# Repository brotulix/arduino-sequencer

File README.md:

# arduino-sequencer
A simple Arduino-based sequencer to turn masthead preamplifier and power amplifier on and off in sequence when beginning and ending transmission, as well as inhibiting transmit on a Yaesu radio (FT-991 or FT-817).

Additions will be switching coax relays to allow co-listening with an SDR during receive period.

## PTT

The same sequencer is intended for 144 and 432 MHz operation, for which I own power amplifiers with opposite PTT controls; one will activate when PTT is pulled high, one will activate when PTT is pulled low. To solve this with the least hassle, I'll control the PTT using a photo diode surrounded by four diodes, and select active high or active low using a toggle switch:

Here, J1 (an RCA socket) connects to the PTT input of either KLM electronics VHF PA or Microwave Modules MML 432/100 UHF PA. SW1 is DPDT and will flip voltages for both the opto-coupler and the pull up/down.

# State machine
So, a state machine may be a useful method to keep track of where one is in the sequence of events going from RX -> TX or TX -> RX.

Maybe some form of table-based state machine to easily add stages and transitioning to the right next state?

Whether I'll use an interrupt to trigger on flank or simply evaluate high/low state in a loop is TBD.

## Initialization / Power-up
The system starts up in an unknown state as of yet. I think it should sets some signals to a safe-ish state immediately, then progresses through some sequence of events to reach a true RX state.

Probably the most important detail is that the PA should be switched on after the sequencer.

> Should the radio be switched on after the sequencer, too, to make sure TX inhibit is on from the start?

## RX -> TX
The sequence when going from RX to TX is something like this:

### RX -> TX -> RX
The special case when TX goes low before during the transition from RX to TX should go something like this:

See *dwell time*.

## TX -> RX
Transitioning from TX back to RX:

### TX -> RX -> TX
The special case where one is transmitting, but then experience a glitch in TX from radio which begins a transition to RX, but then returns to TX during the transition phase.

See *dwell time*.

# Dwell time
> Add a potensiometer/encoder to set the delay for each stage? First design may use the same delay for both entering and leaving transmit state, but perhaps allow for faster delays going one direction or the other later?

Upon entering every state, set a minimum dwell time for that state to allow for energy to stabilize in the system (eg. DC bias for preamp; depending on coax length, you may want a certain minimum delay to allow the rising edge to reach full round-trip).

This may remove the need for a "inter-state" delay period, and depending on what the Radio TX signal is when entering (or exiting) the state determines which direction one goes. So, in principle, by toggling TX line fast enough, it may be possible to stay in the twilight zone between RX and TX indefinitely?

# Blinkenlights
I'm thinking a front panel that shows what state the in- and outputs are in. Should at least help during development when the timing probably is way longer than necessary.

The idea here is that when idle, only the green RX LED should light up. Then, when the radio activates the TX line, the red TX LED lights up, rendering the LED yellow-ish. While both of these LEDs are lit, the individual output LEDs on the side should light up from the bottom up, until all are lit, when the green RX LED goes out and only the red TX LED is lit.

> Perhaps also have the individual stages as red/green LEDs to more clearly illustrate the logic colour-code?

> Perhaps also have a fancy display that shows the current delay count-down for that extra *ooh* and *aah*, at least during development?

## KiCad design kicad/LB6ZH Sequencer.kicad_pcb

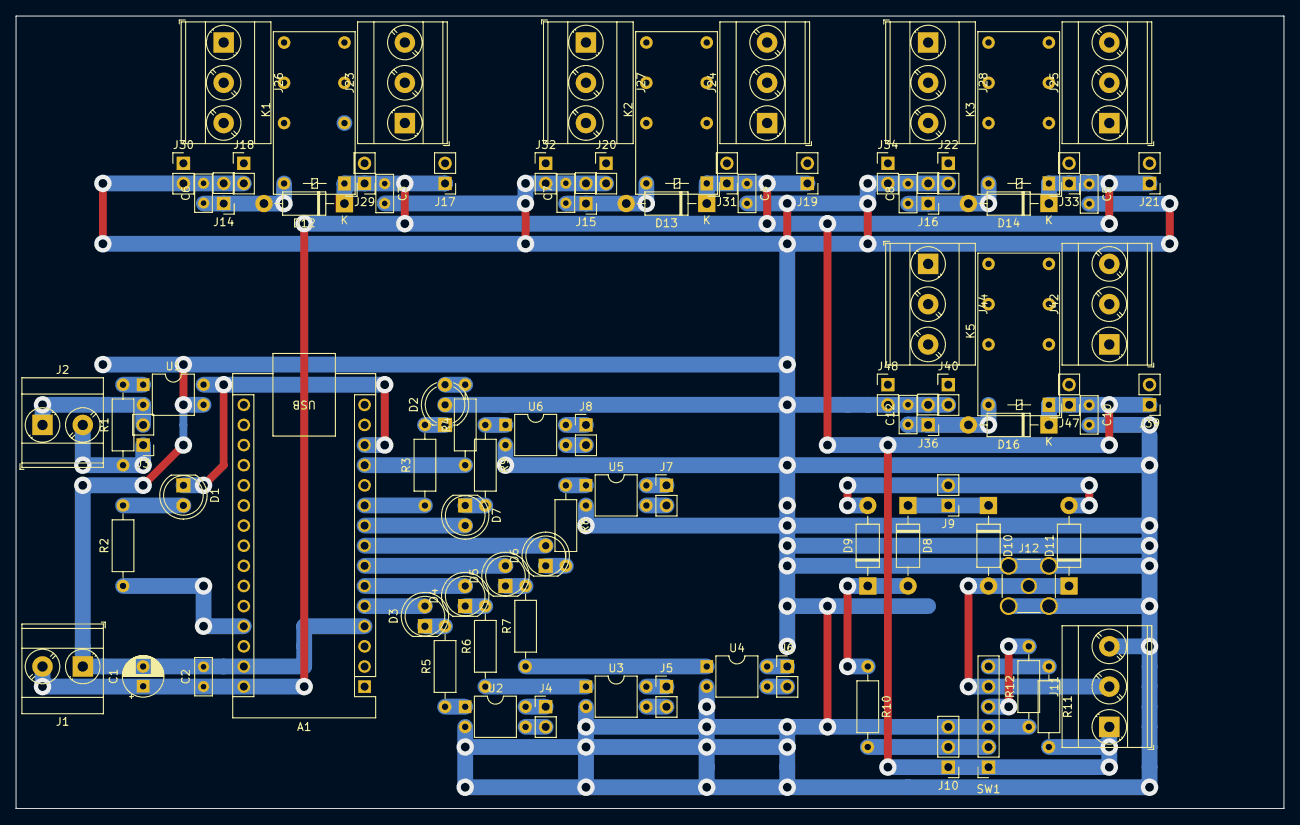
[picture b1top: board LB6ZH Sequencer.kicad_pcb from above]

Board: 2 copper layers, 160.0 x 100.0 mm, 89 parts (0 on the bottom side), 67 nets.

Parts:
A1: Arduino_Nano_Every; Arduino_Nano
C1: 100u; CP_Radial_D5.0mm_P2.50mm
C2, C3, C4, C5, C6, C7, C8, C10, C12: 10n; C_Rect_L4.6mm_W2.0mm_P2.50mm_MKS02_FKP02
D1: RD; LED_D5.0mm_Clear
D2: LED_Dual_AKA; LED_D5.0mm-3
D3, D4, D5, D6, D7: YE; LED_D5.0mm_Clear
D8, D9, D10, D11, D12, D13, D14, D16: 1N4001; D_DO-41_SOD81_P10.16mm_Horizontal
J1: 1x2; TerminalBlock_Phoenix_MKDS-3-2-5.08_1x02_P5.08mm_Horizontal
J2: Screw_Terminal_01x02; TerminalBlock_Phoenix_MKDS-3-2-5.08_1x02_P5.08mm_Horizontal
J3, J4, J5, J6, J7, J8, J9, J14, J15, J16, J17, J18, J19, J20, J21, J22, J29, J30, J31, J32, J33, J34, J36, J39, J40, J47, J48: Conn_01x02; PinHeader_1x02_P2.54mm_Vertical
J10: Conn_01x03; PinHeader_1x03_P2.54mm_Vertical
J11, J23, J24, J25, J26, J27, J28, J42, J44: 1x3; TerminalBlock_Phoenix_MKDS-3-3-5.08_1x03_P5.08mm_Horizontal
J12: RCA; SMA_Amphenol_901-144_Vertical
K1, K2, K3, K5: FINDER-30.22; Relay_DPDT_Finder_30.22
R1: 680R; R_Axial_DIN0207_L6.3mm_D2.5mm_P10.16mm_Horizontal
R2: 150R; R_Axial_DIN0207_L6.3mm_D2.5mm_P10.16mm_Horizontal
R3, R4, R5, R6, R7, R8, R9: 82R; R_Axial_DIN0207_L6.3mm_D2.5mm_P10.16mm_Horizontal
R10: 1k; R_Axial_DIN0207_L6.3mm_D2.5mm_P10.16mm_Horizontal
R11, R12: 10k; R_Axial_DIN0207_L6.3mm_D2.5mm_P10.16mm_Horizontal
SW1: SW_DPDT_x2; PinSocket_1x06_P2.54mm_Vertical
U1, U2, U3, U4, U5, U6: PC817; DIP-4_W7.62mm

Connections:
5V: A1.27 (+5V), R2.1
COAX_A: A1.6 (D3), D4.2 (A)
COAX_B: A1.7 (D4), D5.2 (A)
GND: A1.4 (GND), A1.29 (GND), C1.2, C2.2, C3.2, C4.2, C5.2, C6.2, C7.2, C8.2, C10.2, C12.2, D2.2 (K), J1.1, J10.3, J11.3, J12.2 (Ext), J14.2, J15.2, J16.2, J18.2, J20.2, J22.2, J30.2, J32.2, J34.2, J36.2, J40.2, J48.2, R12.1, SW1.3 (C), U1.3, U2.2, U3.2, U4.2, U5.2, U6.2
unnamed: A1.13 (D10), D1.1 (K), U1.4
unnamed: D1.2 (A), R2.2
unnamed: D2.1 (A1), R3.2
unnamed: D2.3 (A2), R4.2
unnamed: D3.1 (K), R5.2
unnamed: D4.1 (K), R6.2
unnamed: D5.1 (K), R7.2
unnamed: D6.1 (K), R8.2
unnamed: D7.1 (K), R9.2
unnamed: D8.2 (A), D9.1 (K), R10.1
unnamed: D10.2 (A), D11.1 (K), J11.2, J12.1 (In), SW1.5 (B)
unnamed: D9.2 (A), D11.2 (A), J9.2
unnamed: J4.2, U2.3
unnamed: J5.2, U3.3
unnamed: J6.2, U4.3
unnamed: J7.2, U5.3
unnamed: J8.2, U6.3
unnamed: J10.2, R10.2, SW1.2 (B)
unnamed: J17.2, J18.1, J23.2, K1.11
unnamed: J19.2, J20.1, J24.2, K2.11
unnamed: J21.2, J22.1, J25.2, K3.11
unnamed: J23.1, K1.12
unnamed: J23.3, K1.14
unnamed: J24.1, K2.12
unnamed: J24.3, K2.14
unnamed: J25.1, K3.12
unnamed: J25.3, K3.14
unnamed: J26.1, K1.22
unnamed: J26.2, J29.2, J30.1, K1.21
unnamed: J26.3, K1.24
unnamed: J27.1, K2.22
unnamed: J27.2, J31.2, J32.1, K2.21
unnamed: J27.3, K2.24
unnamed: J28.1, K3.22
unnamed: J28.2, J33.2, J34.1, K3.21
unnamed: J28.3, K3.24
unnamed: J39.2, J40.1, J42.2, K5.11
unnamed: J42.1, K5.12
unnamed: J42.3, K5.14
unnamed: J44.1, K5.22
unnamed: J44.2, J47.2, J48.1, K5.21
unnamed: J44.3, K5.24
unnamed: R1.2, U1.1
unnamed: R5.1, U2.1
unnamed: R6.1, U3.1
unnamed: R7.1, U4.1
unnamed: R8.1, U5.1
unnamed: R9.1, U6.1
unnamed: R12.2, SW1.4 (A)
unnamed: R11.1, SW1.6 (C)
OC_COAX_A: C7.1, D13.2 (A), J5.1, J15.1, K2.A2, U3.4
OC_COAX_B: C8.1, D14.2 (A), J6.1, J16.1, K3.A2, U4.4
OC_PA_PTT: D8.1 (K), D10.1 (K), J7.1, J9.1, U5.4
OC_PREAMP: C6.1, D12.2 (A), J4.1, J14.1, K1.A2, U2.4
OC_TX_INHIBIT: C12.1, D16.2 (A), J8.1, J36.1, K5.A2, U6.4
PA_PTT: A1.8 (D5), D6.2 (A)
PREAMP: A1.5 (D2), D3.2 (A)
RX_IND: A1.10 (D7), R3.1
TX_D: J2.2, J3.1, R1.1
TX_GND: J2.1, J3.2, U1.2
TX_IND: A1.12 (D9), R4.1
TX_INHIBIT: A1.9 (D6), D7.2 (A)
VIN: A1.30 (VIN), C1.1, C2.1, C3.1, C4.1, C5.1, C10.1, D12.1 (K), D13.1 (K), D14.1 (K), D16.1 (K), J1.2, J10.1, J11.1, J17.1, J19.1, J21.1, J29.1, J31.1, J33.1, J39.1, J47.1, K1.A1, K2.A1, K3.A1, K5.A1, R11.2, SW1.1 (A)

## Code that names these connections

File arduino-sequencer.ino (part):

#define TEST 1

// @ Todo: maybe use a mega instead for more digital I/O during development?
const int pin_preamp = 2;
const int pin_coax_relay_a = 3;
const int pin_coax_relay_b = 4;
const int pin_pa_ptt = 5;
const int pin_tx_inhibit = 6;
const int pin_rx = 7;
const int pin_tx = 9;
const int pin_txenable = 10;
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//   level,                   delay, pin,                 {down transition,       up transition}
    {LEVEL_UNINITIALIZED,         0, -1,                  {LEVEL_RX,              LEVEL_RX}},
    {LEVEL_RX,               100000, -1,                  {LEVEL_RX,              LEVEL_PREAMP}},
    {LEVEL_PREAMP,           100000, pin_preamp,          {LEVEL_RX,              LEVEL_COAX_RELAY_A}},
    {LEVEL_COAX_RELAY_A,     100000, pin_coax_relay_a,    {LEVEL_PREAMP,          LEVEL_COAX_RELAY_B}},
    {LEVEL_COAX_RELAY_B,     100000, pin_coax_relay_b,    {LEVEL_COAX_RELAY_A,    LEVEL_PA_PTT}},
    {LEVEL_PA_PTT,           100000, pin_pa_ptt,          {LEVEL_COAX_RELAY_B,    LEVEL_TX_INHIBIT}},
    {LEVEL_TX_INHIBIT,       100000, pin_tx_inhibit,      {LEVEL_PA_PTT,          LEVEL_TX}},
    {LEVEL_TX,               100000, -1,                  {LEVEL_TX_INHIBIT,      LEVEL_TX}}
};

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
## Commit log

2023-06-28 Updated README.md.
2023-07-02 State machine doc begun
2023-07-02 Added PTT circuit
2023-07-02 Readme edit.
2023-07-02 Minor readme edit.
2023-07-02 Some text on the flashy bits
2023-07-02 First beginnings of a program skeleton.
2023-07-02 Baby steps. VS Code Arduino extension apparently doesn't play well with remote sessions, so have to resort to traditional SSH/X.
2023-07-07 Something like this? Overly complicated, but meh.
2023-07-08 Yay! It works!
2023-07-08 Stop tracking arduino.json.
2023-07-08 Add .vscode to gitignore
2023-07-08 It werks! (#1)
    * Baby steps.
    VS Code Arduino extension apparently doesn't play well with remote sessions, so have to resort to traditional SSH/X.
    * Something like this?
    Overly complicated, but meh.
    * Yay! It works!
    * Stop tracking arduino.json.
2023-07-08 Commented out loop interval and debug.
2023-07-08 Commented out loop interval and debug. (#2)
    Should be a bit snappier in reacting to TX Enable, now.
    Still randomly chosen interval for steps, though.
2023-07-08 Removed unused transition table. RX and TX LED on during transition.
2023-07-15 Removed unused transition table. (#3)
    RX and TX LED on during transition.
2023-07-15 Added PDFs of schematic and perf board prototype layout.
2023-07-15 Added PDFs of schematic and perf board prototype layout. (#4)
2023-07-24 Changed polarity of TX line to match radio.
2023-07-24 Removed some debug printouts.
2023-07-24 Added KiCad project with prototype breadboard layout.
2023-07-27 Panel designs in SolidEdge 2D.
2023-07-27 Updates to kicad PCB after prototype assembly.
2023-07-27 Fixed a net that was grounded in error.
2023-07-27 Minor corrections after applying mods on prototype.
